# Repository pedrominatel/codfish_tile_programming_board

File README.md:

# Codfish Tile Programming Board

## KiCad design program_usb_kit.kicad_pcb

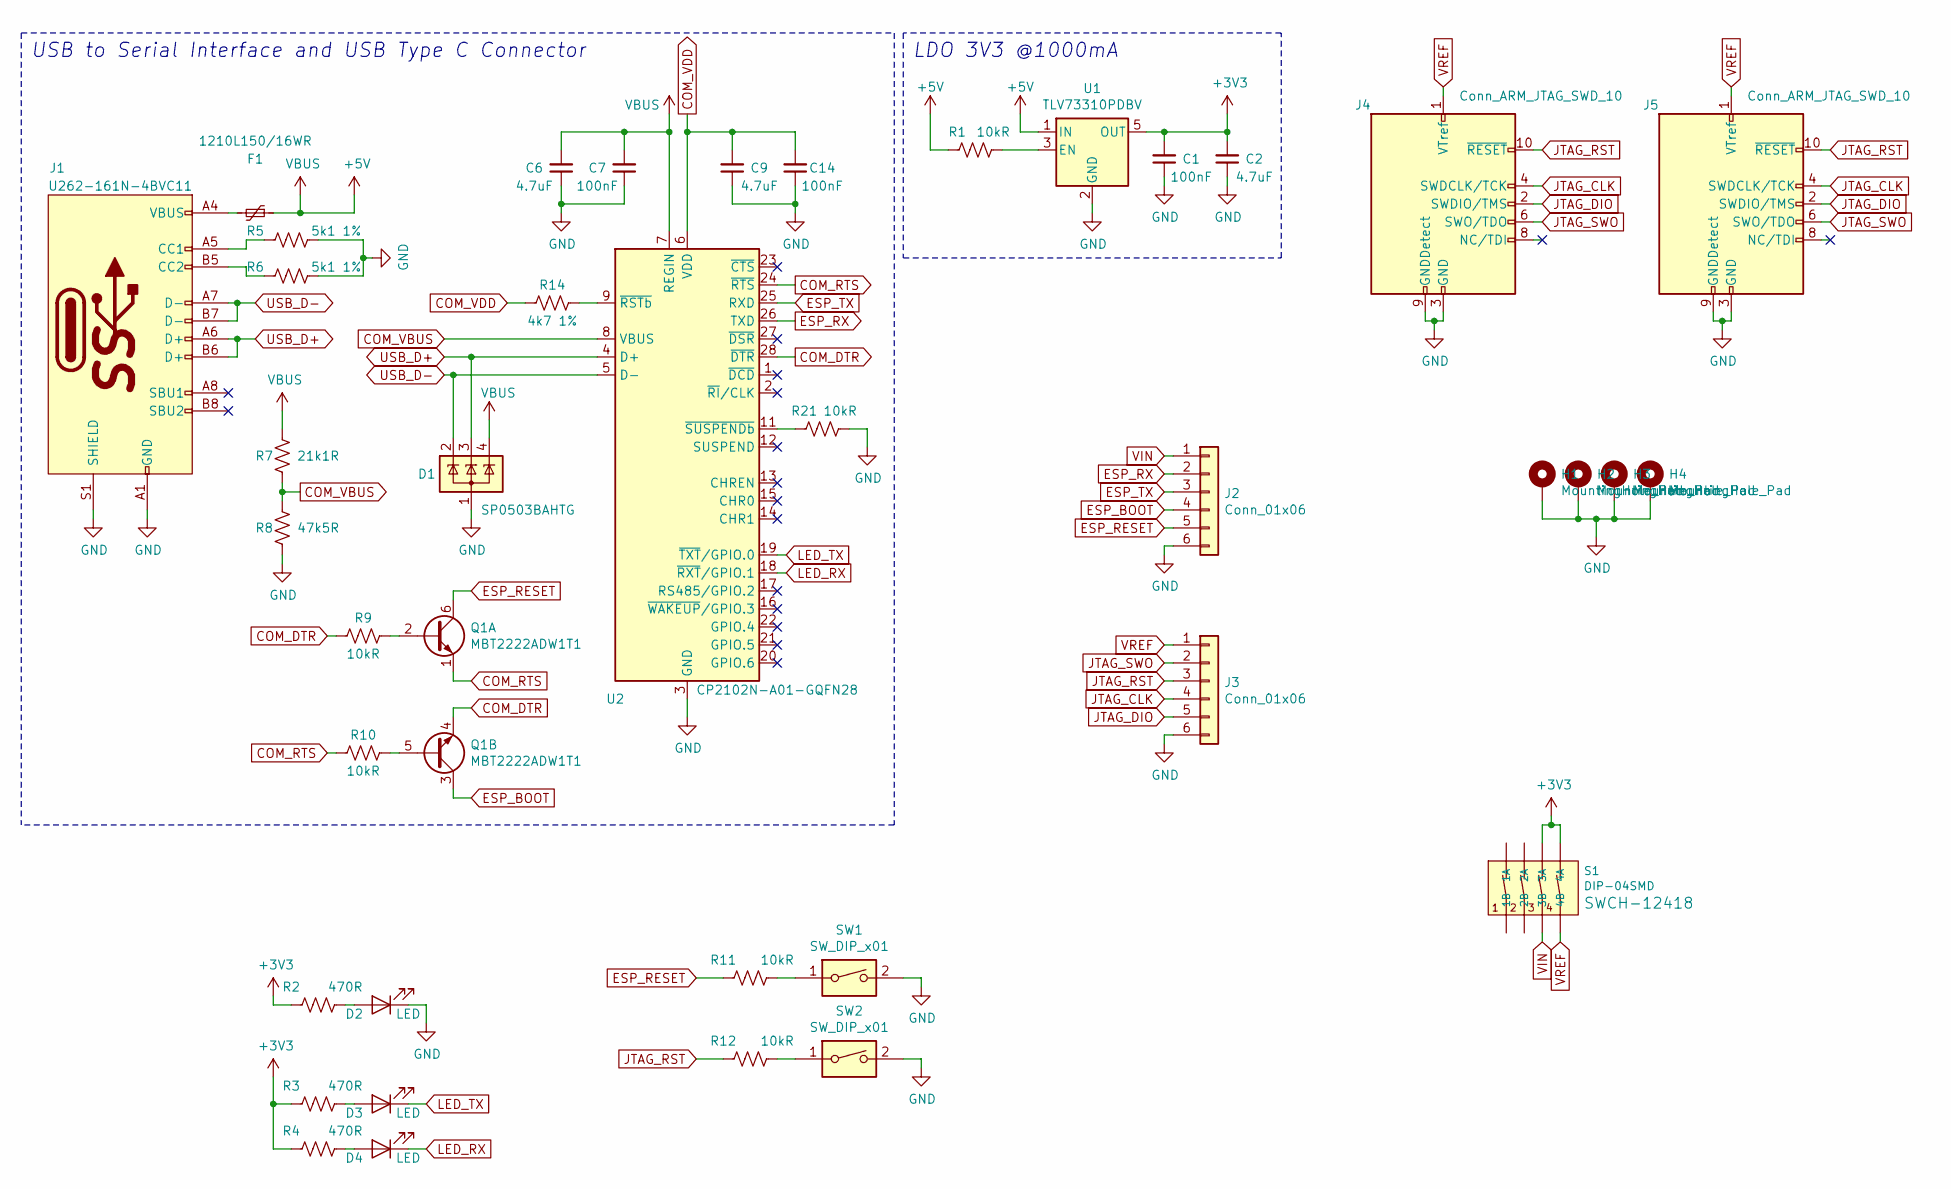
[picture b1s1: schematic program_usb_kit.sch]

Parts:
C1, C7, C14: 100nF; C_0603_1608Metric
C2, C6, C9: 4.7uF; C_0603_1608Metric
D1: SP0503BAHTG; SOT-143
D2, D3, D4: LED; LED_0805_2012Metric
F1: 1210L150/16WR; 1210
H1, H2, H3, H4: MountingHole_Pad; MountingHole_2.5mm_Pad_Via
J1: U262-161N-4BVC11; USB_C_Receptacle_Palconn_UTC16-G
J2, J3: Conn_01x06; TE_84952-6_1x06-1MP_P1.0mm_Horizontal
J4: Conn_ARM_JTAG_SWD_10; PinHeader_2x05_P1.27mm_Vertical_SMD
J5: Conn_ARM_JTAG_SWD_10; PinHeader_2x05_P1.27mm_Vertical
Q1: MBT2222ADW1T1; SOT-363_SC-70-6
R1, R9, R10, R21: 10kR; R_0402_1005Metric
R2, R3, R4: 470R; R_0603_1608Metric
R5, R6: 5k1 1%; R_0402_1005Metric
R7: 21k1R; R_0603_1608Metric
R8: 47k5R; R_0603_1608Metric
R11, R12: 10kR; R_0603_1608Metric
R14: 4k7 1%; R_0402_1005Metric
S1: DIP-04SMD; DIPSWITCH-04-SMD
SW1, SW2: SW_DIP_x01; TACTILE_SWITCH_SMD_6.0X3.5MM
U1: TLV73310PDBV; SOT-23-5
U2: CP2102N-A01-GQFN28; QFN-28-1EP_5x5mm_P0.5mm_EP3.35x3.35mm

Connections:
+3V3: C1.2, C2.2, R2.1, R3.1, R4.1, S1.3 (3A), S1.4 (4A), U1.5 (OUT)
+5V: C6.2, C7.2, D1.4 (K), F1.1, R1.1, R7.2, U1.1 (IN), U2.7 (REGIN)
COM_DTR: Q1.4 (E2), R9.2, U2.28 (~DTR)
COM_RTS: Q1.1 (E1), R10.2, U2.24 (~RTS)
COM_VBUS: R7.1, R8.2, U2.8 (VBUS)
COM_VDD: C9.2, C14.2, R14.1, U2.6 (VDD)
ESP_BOOT: J2.4, Q1.3 (C2)
ESP_RESET: J2.5, Q1.6 (C1), R11.1
ESP_RX: J2.2, U2.26 (TXD)
ESP_TX: J2.3, U2.25 (RXD)
GND: C1.1, C2.1, C6.1, C7.1, C9.1, C14.1, D1.1 (A), D2.1 (K), H1.1, H2.1, H3.1, H4.1, J1.A1 (GND), J1.A12 (GND), J1.B1 (GND), J1.B12 (GND), J1.S1 (SHIELD), J2.6, J3.6, J4.3 (GND), J4.5 (GND), J4.9 (GNDDetect), J5.3 (GND), J5.5 (GND), J5.9 (GNDDetect), R5.1, R6.1, R8.1, R21.2, SW1.2, SW2.2, U1.2 (GND), U2.3 (GND), U2.29 (GND)
JTAG_CLK: J3.4, J4.4 (SWDCLK/TCK), J5.4 (SWDCLK/TCK)
JTAG_DIO: J3.5, J4.2 (SWDIO/TMS), J5.2 (SWDIO/TMS)
JTAG_RST: J3.3, J4.10 (~RESET~), J5.10 (~RESET~), R12.1
JTAG_SWO: J3.2, J4.6 (SWO/TDO), J5.6 (SWO/TDO)
LED_RX: D4.1 (K), U2.18 (~RXT~/GPIO.1)
LED_TX: D3.1 (K), U2.19 (~TXT~/GPIO.0)
unnamed: D2.2 (A), R2.2
unnamed: D3.2 (A), R3.2
unnamed: D4.2 (A), R4.2
unnamed: F1.2, J1.A4 (VBUS), J1.A9 (VBUS), J1.B4 (VBUS), J1.B9 (VBUS)
unnamed: J1.A5 (CC1), R5.2
unnamed: J1.B5 (CC2), R6.2
unnamed: Q1.2 (B1), R9.1
unnamed: Q1.5 (B2), R10.1
unnamed: R1.2, U1.3 (EN)
unnamed: R11.2, SW1.1
unnamed: R12.2, SW2.1
unnamed: R14.2, U2.9 (~RSTb)
unnamed: R21.1, U2.11 (~SUSPENDb)
USB_D+: D1.3 (K), J1.A6 (D+), J1.B6 (D+), U2.4 (D+)
USB_D-: D1.2 (K), J1.A7 (D-), J1.B7 (D-), U2.5 (D-)
VIN: J2.1, S1.6 (3B)
VREF: J3.1, J4.1 (VTref), J5.1 (VTref), S1.5 (4B)

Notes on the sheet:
USB to Serial Interface and USB Type C Connector
LDO 3V3 @1000mA

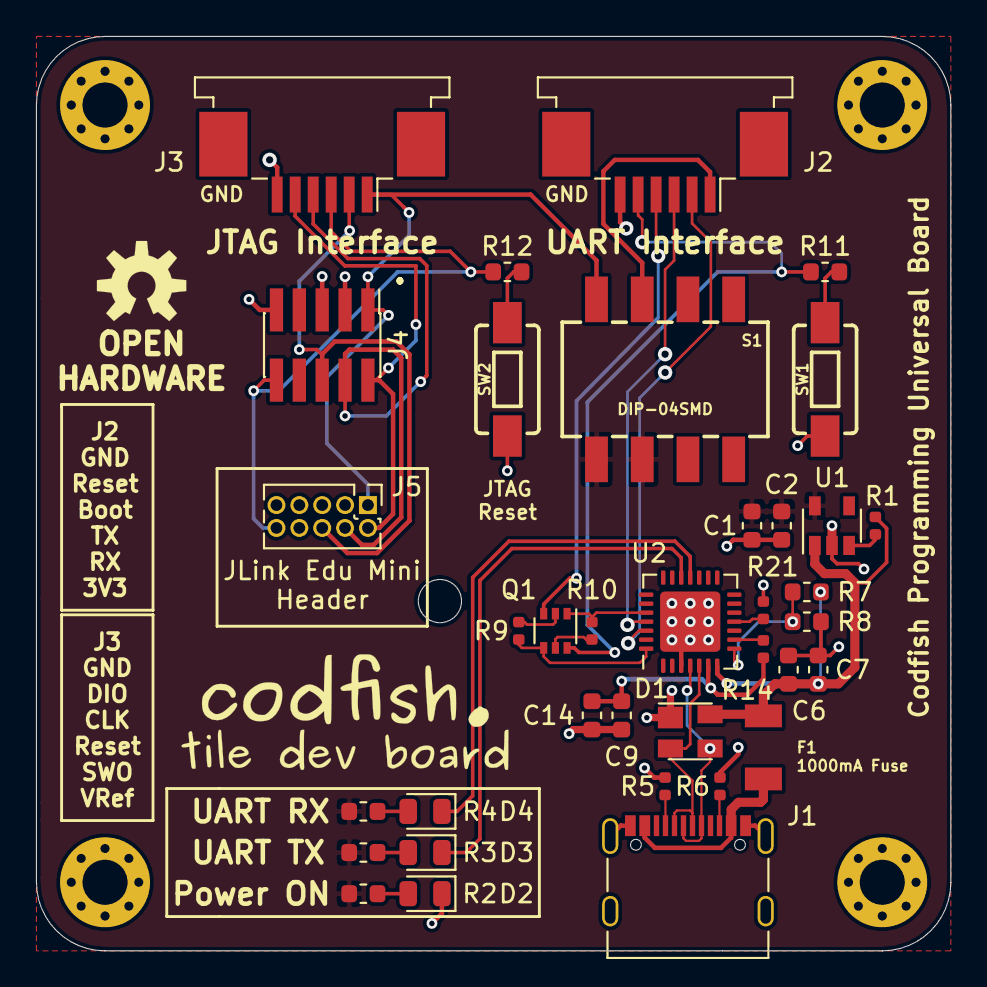
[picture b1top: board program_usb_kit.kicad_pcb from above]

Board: 2 copper layers, 50.8 x 50.8 mm, 40 parts (0 on the bottom side), 34 nets.

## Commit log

2020-06-30 Project added
